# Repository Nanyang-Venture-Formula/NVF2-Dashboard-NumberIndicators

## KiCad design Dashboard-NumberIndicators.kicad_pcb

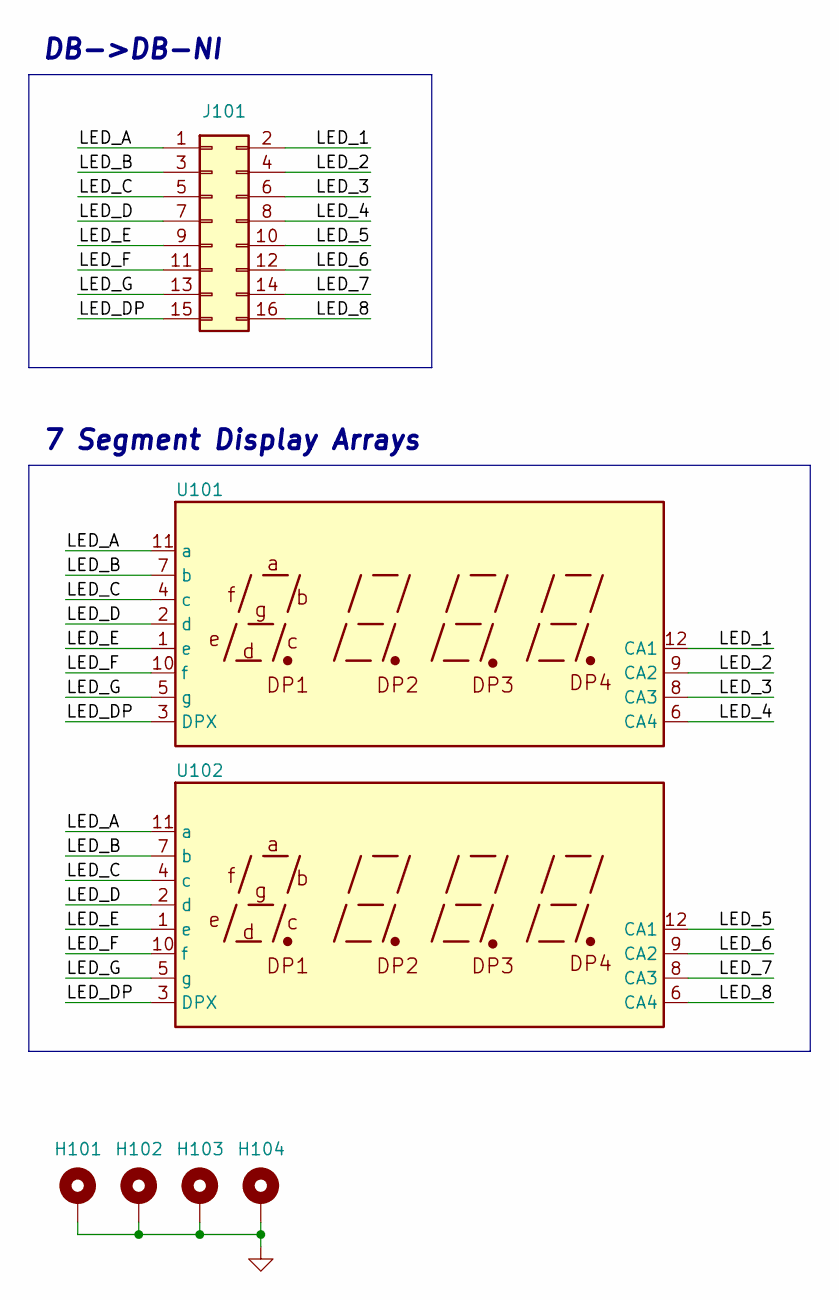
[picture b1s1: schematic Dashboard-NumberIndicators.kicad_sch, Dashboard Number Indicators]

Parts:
H101, H102, H103, H104: MountingHole_Pad; MountingHole_3.2mm_M3_DIN965_Pad_TopBottom
J101: Conn_02x08_Odd_Even; JST_PHD_B16B-PHDSS_2x08_P2.00mm_Vertical
U101, U102: CA56-12EWA

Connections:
/LED_1: J101.2, U101.12 (CA1)
/LED_2: J101.4, U101.9 (CA2)
/LED_3: J101.6, U101.8 (CA3)
/LED_4: J101.8, U101.6 (CA4)
/LED_5: J101.10, U102.12 (CA1)
/LED_6: J101.12, U102.9 (CA2)
/LED_7: J101.14, U102.8 (CA3)
/LED_8: J101.16, U102.6 (CA4)
/LED_A: J101.1, U101.11 (a), U102.11 (a)
/LED_B: J101.3, U101.7 (b), U102.7 (b)
/LED_C: J101.5, U101.4 (c), U102.4 (c)
/LED_D: J101.7, U101.2 (d), U102.2 (d)
/LED_DP: J101.15, U101.3 (DPX), U102.3 (DPX)
/LED_E: J101.9, U101.1 (e), U102.1 (e)
/LED_F: J101.11, U101.10 (f), U102.10 (f)
/LED_G: J101.13, U101.5 (g), U102.5 (g)
GND: H101.1, H102.1, H103.1, H104.1

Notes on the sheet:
DB->DB-NI
7 Segment Display Arrays

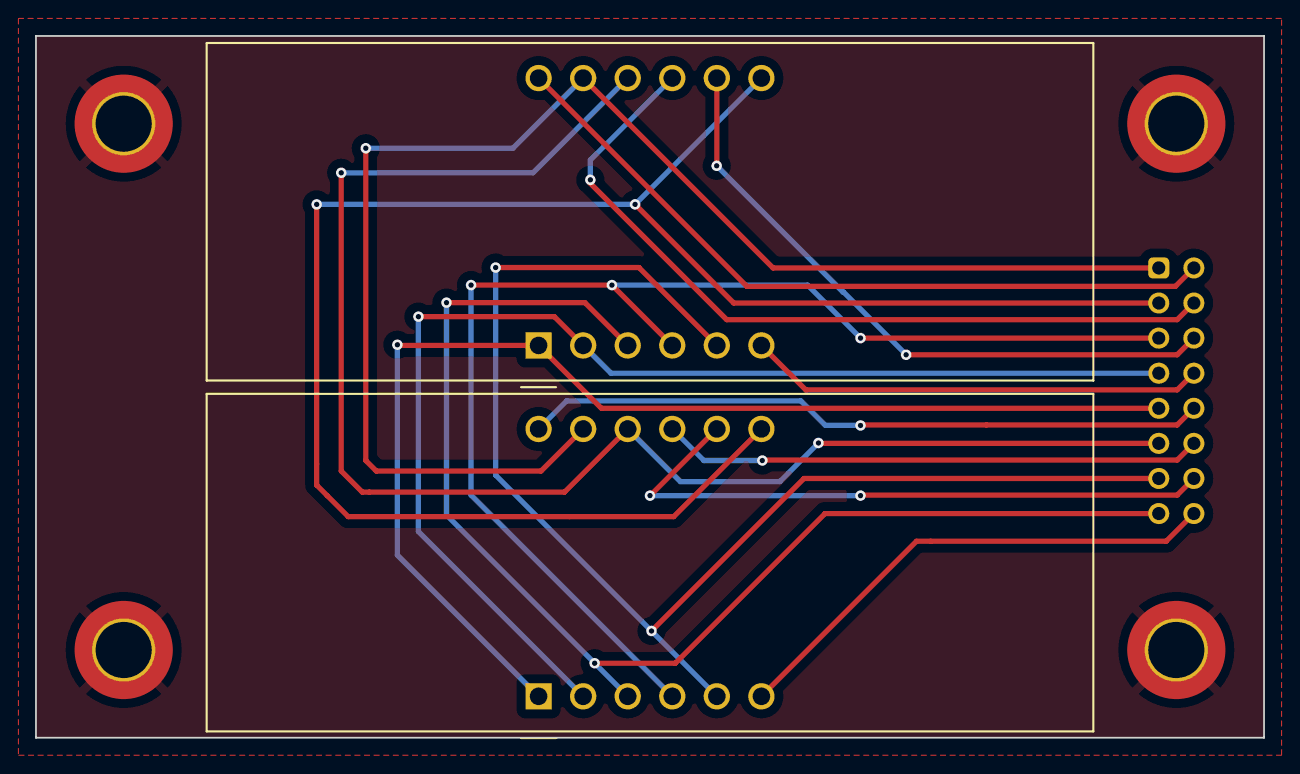
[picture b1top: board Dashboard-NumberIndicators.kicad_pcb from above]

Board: 2 copper layers, 70.0 x 40.0 mm, 7 parts (1 on the bottom side), 17 nets.

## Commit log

2024-01-23 Initialize gh-pages
2024-01-23 Moving files docs/* LICENSE using main
2024-01-23 Deploying to gh-pages from @ Nanyang-Venture-Formula/NVF2-Dashboard-NumberIndicators@1c40b4b9c7f5e054028945d38ac623d3e6146117 🚀
2024-01-23 Deploying to gh-pages from @ Nanyang-Venture-Formula/NVF2-Dashboard-NumberIndicators@e6f17c3b2ea14650b0424e287b97fd7b3274f459 🚀
2024-01-23 refactored
2024-01-23 Deploying to gh-pages from @ Nanyang-Venture-Formula/NVF2-Dashboard-NumberIndicators@87064c77895f9d68e9bc7460f948ac554ac87ad6 🚀
2024-01-24 updated ignore
2024-01-24 Deploying to gh-pages from @ Nanyang-Venture-Formula/NVF2-Dashboard-NumberIndicators@db07b9849bb3b6344eb31999bd752ca1de3a01ff 🚀
2024-01-24 updated gitignore
2024-01-24 Deploying to gh-pages from @ Nanyang-Venture-Formula/NVF2-Dashboard-NumberIndicators@5f808a152563f280980152fee841583a9ab15e0c 🚀
2024-02-02 updated bom
